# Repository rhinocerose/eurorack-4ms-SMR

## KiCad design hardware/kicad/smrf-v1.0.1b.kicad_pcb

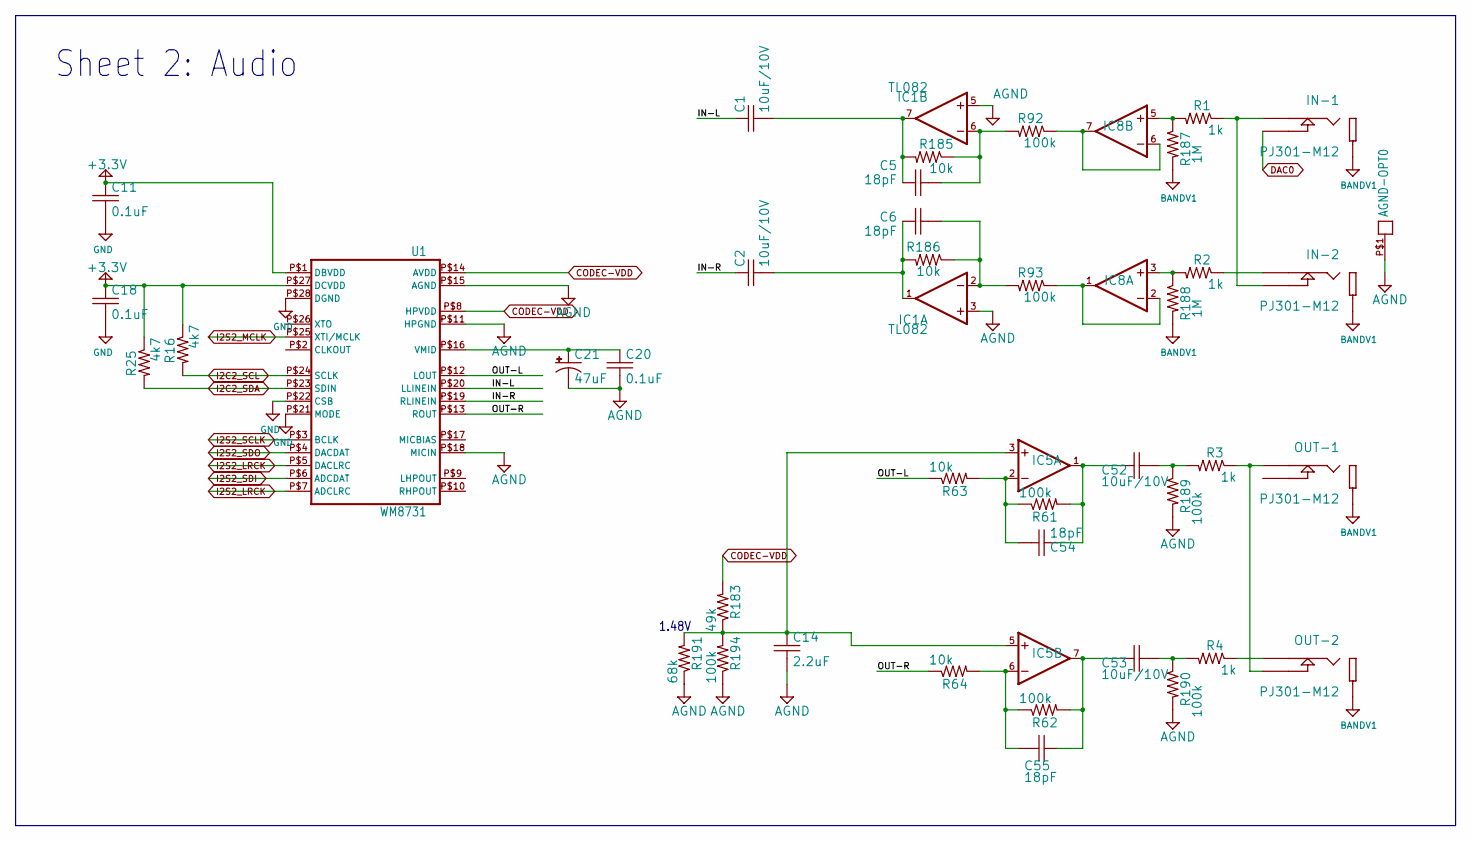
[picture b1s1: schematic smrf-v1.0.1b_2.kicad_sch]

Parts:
AGND-OPT0: PAD-06
C1, C2, C52, C53: 10uF/10V; C0603
C5, C6, C54, C55: 18pF; C0603
C11, C18, C20: 0.1uF; C0603
C14: 2.2uF; C0603
C21: 47uF; C-POL-5
IC1, IC5, IC8: TL082; TSSOP8
IN-1, IN-2: PJ301-M12; PJ301M-12-FIX
OUT-1, OUT-2: PJ301-M12; PJ301M-12-FIX
R1, R2, R3, R4: 1k; R0603
R16, R25: 4k7; R0603
R61, R62, R92, R93, R189, R190, R194: 100k; R0603
R63, R64, R185, R186: 10k; R0603
R183: 49k; R0603
R187, R188: 1M; R0603
R191: 68k; R0603
U1: WM8731; 28-SSOP

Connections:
+3.3V: C11.1, C18.1, R16.1, R25.1, U1.P$1 (DBVDD), U1.P$27 (DCVDD); also elsewhere on the board
AGND: AGND-OPT0.P$1, C14.2, C20.2, C21.-, IC1.3 (+IN), IC1.5 (+IN), R189.2, R190.2, R191.1, R194.1, U1.P$11 (HPGND), U1.P$15 (AGND), U1.P$18 (MICIN); also elsewhere on the board
CODEC-VDD: R183.2, U1.P$8 (HPVDD), U1.P$14 (AVDD); also elsewhere on the board
DAC0: IN-1.3 (TIP-SW); also elsewhere on the board
GND: C11.2, C18.2, IN-1.2 (SLEEVE), IN-2.2 (SLEEVE), OUT-1.2 (SLEEVE), OUT-2.2 (SLEEVE), R187.2, R188.2, U1.P$21 (MODE), U1.P$22 (CSB), U1.P$28 (DGND); also elsewhere on the board
I2C2_SCL: R16.2, U1.P$24 (SCLK); also elsewhere on the board
I2C2_SDA: R25.2, U1.P$23 (SDIN); also elsewhere on the board
I2S2_LRCK: U1.P$5 (DACLRC), U1.P$7 (ADCLRC); also elsewhere on the board
I2S2_MCLK: U1.P$25 (XTI/MCLK); also elsewhere on the board
I2S2_SCLK: U1.P$3 (BCLK); also elsewhere on the board
I2S2_SDI: U1.P$6 (ADCDAT); also elsewhere on the board
I2S2_SDO: U1.P$4 (DACDAT); also elsewhere on the board
IN-L: C1.1, U1.P$20 (LLINEIN)
IN-R: C2.1, U1.P$19 (RLINEIN)
unnamed: OUT-2.1 (TIP), R4.1
unnamed: OUT-1.1 (TIP), OUT-2.3 (TIP-SW), R3.1
unnamed: IN-2.1 (TIP), R2.1
unnamed: C6.2, IC1.2 (-IN), R93.2, R186.1
unnamed: C20.1, C21.+, U1.P$16 (VMID)
unnamed: C54.2, IC5.2 (-IN), R61.1, R63.2
unnamed: C5.2, IC1.6 (-IN), R92.2, R185.1
unnamed: IN-1.1 (TIP), IN-2.3 (TIP-SW), R1.1
unnamed: C1.2, C5.1, IC1.7 (OUT), R185.2
unnamed: C2.2, C6.1, IC1.1 (OUT), R186.2
unnamed: C52.1, C54.1, IC5.1 (OUT), R61.2
unnamed: C55.2, IC5.6 (-IN), R62.1, R64.2
unnamed: C53.1, C55.1, IC5.7 (OUT), R62.2
unnamed: IC8.5 (+IN), R1.2, R187.1
unnamed: IC8.3 (+IN), R2.2, R188.1
unnamed: IC8.6 (-IN), IC8.7 (OUT), R92.1
unnamed: IC8.1 (OUT), IC8.2 (-IN), R93.1
unnamed: C52.2, R3.2, R189.1
unnamed: C53.2, R4.2, R190.1
OUT-L: R63.1, U1.P$12 (LOUT)
OUT-R: R64.1, U1.P$13 (ROUT)
VOUTOFFSET: C14.1, IC5.3 (+IN), IC5.5 (+IN), R183.1, R191.2, R194.2

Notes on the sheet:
Sheet 2: Audio
1.48V

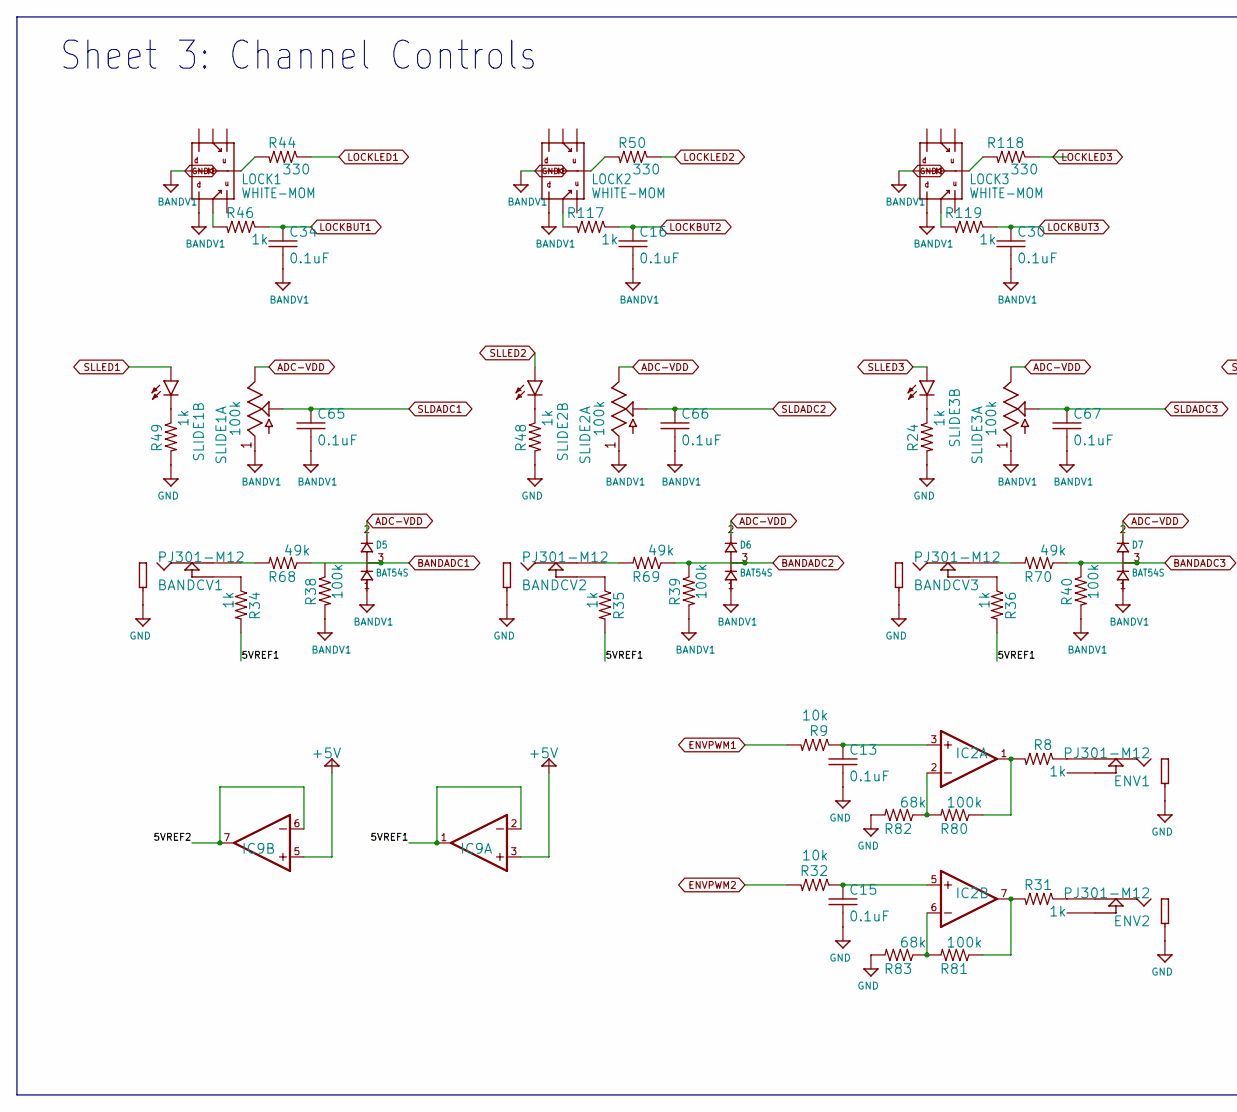
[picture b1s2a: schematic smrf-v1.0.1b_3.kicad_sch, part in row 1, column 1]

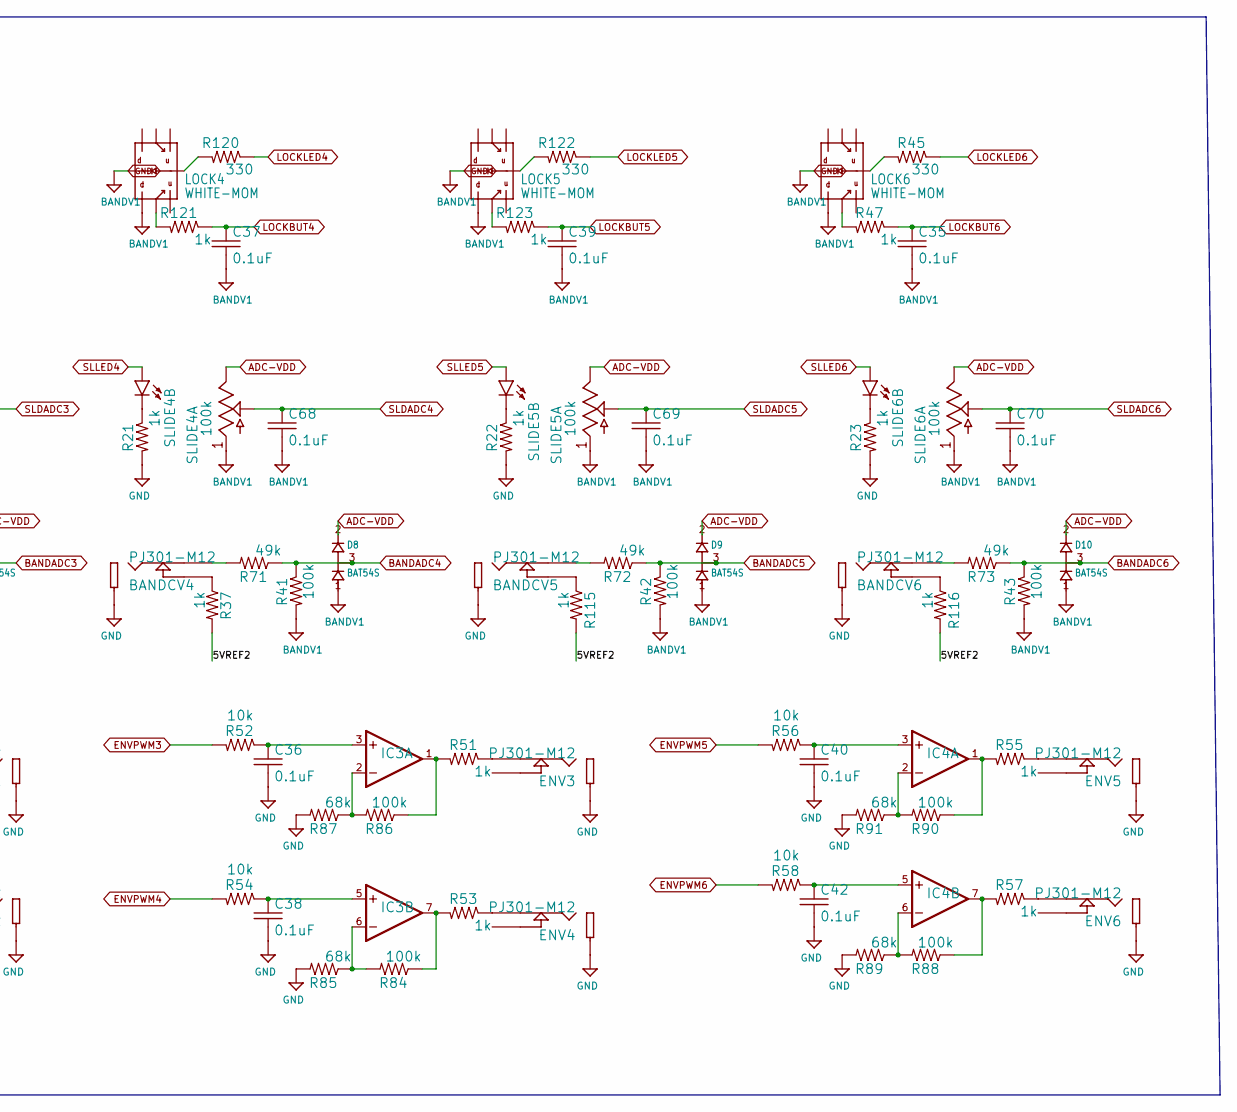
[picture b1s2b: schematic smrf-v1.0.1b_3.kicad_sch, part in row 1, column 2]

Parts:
BANDCV1, BANDCV2, BANDCV3, BANDCV4, BANDCV5, BANDCV6: PJ301-M12; PJ301M-12-FIX
C13, C15, C16, C30, C34, C35, C36, C37, C38, C39, C40, C42, C65, C66, C67, C68, C69, C70: 0.1uF; C0603
D5, D6, D7, D8, D9, D10: BAT54S; SOT23
ENV1, ENV2, ENV3, ENV4, ENV5, ENV6: PJ301-M12; PJ301M-12-FIX
IC2, IC3, IC4, IC9: TL082; TSSOP8
LOCK1, LOCK2, LOCK3, LOCK4, LOCK5, LOCK6: WHITE-MOM; BUTTON-LED-PB61303
R8, R21, R22, R23, R24, R31, R34, R35, R36, R37, R46, R47, R48, R49, R51, R53, R55, R57, R115, R116, R117, R119, R121, R123: 1k; R0603
R9, R32, R52, R54, R56, R58: 10k; R0603
R38, R39, R40, R41, R42, R43, R80, R81, R84, R86, R88, R90: 100k; R0603
R44, R45, R50, R118, R120, R122: 330; R0603
R68, R69, R70, R71, R72, R73: 49k; R0603
R82, R83, R85, R87, R89, R91: 68k; R0603
SLIDE1, SLIDE2, SLIDE3, SLIDE4, SLIDE5, SLIDE6: 100k; POT-SLIDER-ALPHA-RA2045F-20

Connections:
5VREF1: IC9.1 (OUT), IC9.2 (-IN), R34.2, R35.2, R36.2
5VREF2: IC9.6 (-IN), IC9.7 (OUT), R37.2, R115.2, R116.2
+5V: IC9.3 (+IN), IC9.5 (+IN); also elsewhere on the board
ADC-VDD: D5.2 (CATHODE), D6.2 (CATHODE), D7.2 (CATHODE), D8.2 (CATHODE), D9.2 (CATHODE), D10.2 (CATHODE), SLIDE1.P$3 (3), SLIDE2.P$3 (3), SLIDE3.P$3 (3), SLIDE4.P$3 (3), SLIDE5.P$3 (3), SLIDE6.P$3 (3); also elsewhere on the board
BANDADC1: D5.3 (COMMON), R38.1, R68.1; also elsewhere on the board
BANDADC2: D6.3 (COMMON), R39.1, R69.1; also elsewhere on the board
BANDADC3: D7.3 (COMMON), R40.1, R70.1; also elsewhere on the board
BANDADC4: D8.3 (COMMON), R41.1, R71.1; also elsewhere on the board
BANDADC5: D9.3 (COMMON), R42.1, R72.1; also elsewhere on the board
BANDADC6: D10.3 (COMMON), R43.1, R73.1; also elsewhere on the board
ENVPWM1: R9.2; also elsewhere on the board
ENVPWM2: R32.2; also elsewhere on the board
ENVPWM3: R52.2; also elsewhere on the board
ENVPWM4: R54.2; also elsewhere on the board
ENVPWM5: R56.2; also elsewhere on the board
ENVPWM6: R58.2; also elsewhere on the board
GND: BANDCV1.2 (SLEEVE), BANDCV2.2 (SLEEVE), BANDCV3.2 (SLEEVE), BANDCV4.2 (SLEEVE), BANDCV5.2 (SLEEVE), BANDCV6.2 (SLEEVE), C13.2, C15.2, C16.2, C30.2, C34.2, C35.2, C36.2, C37.2, C38.2, C39.2, C40.2, C42.2, C65.2, C66.2, C67.2, C68.2, C69.2, C70.2, D5.1 (ANODE), D6.1 (ANODE), D7.1 (ANODE), D8.1 (ANODE), D9.1 (ANODE), D10.1 (ANODE), ENV1.2 (SLEEVE), ENV2.2 (SLEEVE), ENV3.2 (SLEEVE), ENV4.2 (SLEEVE), ENV5.2 (SLEEVE), ENV6.2 (SLEEVE), LOCK1.P$6, LOCK1.P$8, LOCK2.P$6, LOCK2.P$8, LOCK3.P$6, LOCK3.P$8, LOCK4.P$6, LOCK4.P$8, LOCK5.P$6, LOCK5.P$8, LOCK6.P$6, LOCK6.P$8, R21.2, R22.2, R23.2, R24.2, R38.2, R39.2, R40.2, R41.2, R42.2, R43.2, R48.2, R49.2, R82.2, R83.2, R85.2, R87.2, R89.2, R91.2, SLIDE1.P$1 (1), SLIDE2.P$1 (1), SLIDE3.P$1 (1), SLIDE4.P$1 (1), SLIDE5.P$1 (1), SLIDE6.P$1 (1); also elsewhere on the board
LOCKBUT1: C34.1, R46.1; also elsewhere on the board
LOCKBUT2: C16.1, R117.1; also elsewhere on the board
LOCKBUT3: C30.1, R119.1; also elsewhere on the board
LOCKBUT4: C37.1, R121.1; also elsewhere on the board
LOCKBUT5: C39.1, R123.1; also elsewhere on the board
LOCKBUT6: C35.1, R47.1; also elsewhere on the board
LOCKLED1: R44.1; also elsewhere on the board
LOCKLED2: R50.1; also elsewhere on the board
LOCKLED3: R118.1; also elsewhere on the board
LOCKLED4: R120.1; also elsewhere on the board
LOCKLED5: R122.1; also elsewhere on the board
LOCKLED6: R45.1; also elsewhere on the board
unnamed: ENV1.1 (TIP), R8.1
unnamed: BANDCV1.3 (TIP-SW), R34.1
unnamed: BANDCV2.3 (TIP-SW), R35.1
unnamed: BANDCV3.3 (TIP-SW), R36.1
unnamed: BANDCV4.3 (TIP-SW), R37.1
unnamed: BANDCV5.3 (TIP-SW), R115.1
unnamed: BANDCV6.3 (TIP-SW), R116.1
unnamed: R21.1, SLIDE4.P$LEDC (C)
unnamed: R22.1, SLIDE5.P$LEDC (C)
unnamed: LOCK2.P$7, R50.2
unnamed: LOCK2.P$5, R117.2
unnamed: C13.1, IC2.3 (+IN), R9.1
unnamed: R23.1, SLIDE6.P$LEDC (C)
unnamed: BANDCV1.1 (TIP), R68.2
unnamed: LOCK1.P$7, R44.2
unnamed: BANDCV2.1 (TIP), R69.2
unnamed: LOCK6.P$7, R45.2
unnamed: R24.1, SLIDE3.P$LEDC (C)
unnamed: BANDCV3.1 (TIP), R70.2
unnamed: LOCK1.P$5, R46.2
unnamed: R48.1, SLIDE2.P$LEDC (C)
unnamed: BANDCV4.1 (TIP), R71.2
unnamed: LOCK6.P$5, R47.2
unnamed: R49.1, SLIDE1.P$LEDC (C)
unnamed: BANDCV5.1 (TIP), R72.2
unnamed: BANDCV6.1 (TIP), R73.2
unnamed: IC2.1 (OUT), R8.2, R80.1
unnamed: ENV2.1 (TIP), R31.1
unnamed: C15.1, IC2.5 (+IN), R32.1
unnamed: IC2.7 (OUT), R31.2, R81.1
unnamed: ENV3.1 (TIP), R51.1
unnamed: C36.1, IC3.3 (+IN), R52.1
unnamed: IC3.1 (OUT), R51.2, R86.1
unnamed: ENV4.1 (TIP), R53.1
unnamed: C38.1, IC3.5 (+IN), R54.1
unnamed: IC3.7 (OUT), R53.2, R84.1
unnamed: ENV5.1 (TIP), R55.1
unnamed: C40.1, IC4.3 (+IN), R56.1
unnamed: IC4.1 (OUT), R55.2, R90.1
unnamed: ENV6.1 (TIP), R57.1
unnamed: C42.1, IC4.5 (+IN), R58.1
unnamed: IC4.7 (OUT), R57.2, R88.1
unnamed: IC4.2 (-IN), R90.2, R91.1
unnamed: IC3.6 (-IN), R84.2, R85.1
unnamed: IC3.2 (-IN), R86.2, R87.1
unnamed: IC4.6 (-IN), R88.2, R89.1
unnamed: IC2.6 (-IN), R81.2, R83.1
unnamed: IC2.2 (-IN), R80.2, R82.1
unnamed: LOCK3.P$7, R118.2
unnamed: LOCK3.P$5, R119.2
unnamed: LOCK4.P$7, R120.2
unnamed: LOCK4.P$5, R121.2
unnamed: LOCK5.P$7, R122.2
unnamed: LOCK5.P$5, R123.2
SLDADC1: C65.1, SLIDE1.P$2 (2); also elsewhere on the board
SLDADC2: C66.1, SLIDE2.P$2 (2); also elsewhere on the board
SLDADC3: C67.1, SLIDE3.P$2 (2); also elsewhere on the board
SLDADC4: C68.1, SLIDE4.P$2 (2); also elsewhere on the board
SLDADC5: C69.1, SLIDE5.P$2 (2); also elsewhere on the board
SLDADC6: C70.1, SLIDE6.P$2 (2); also elsewhere on the board
SLLED1: SLIDE1.P$LEDA (A); also elsewhere on the board
SLLED2: SLIDE2.P$LEDA (A); also elsewhere on the board
SLLED3: SLIDE3.P$LEDA (A); also elsewhere on the board
SLLED4: SLIDE4.P$LEDA (A); also elsewhere on the board
SLLED5: SLIDE5.P$LEDA (A); also elsewhere on the board
SLLED6: SLIDE6.P$LEDA (A); also elsewhere on the board

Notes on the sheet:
Sheet 3: Channel Controls

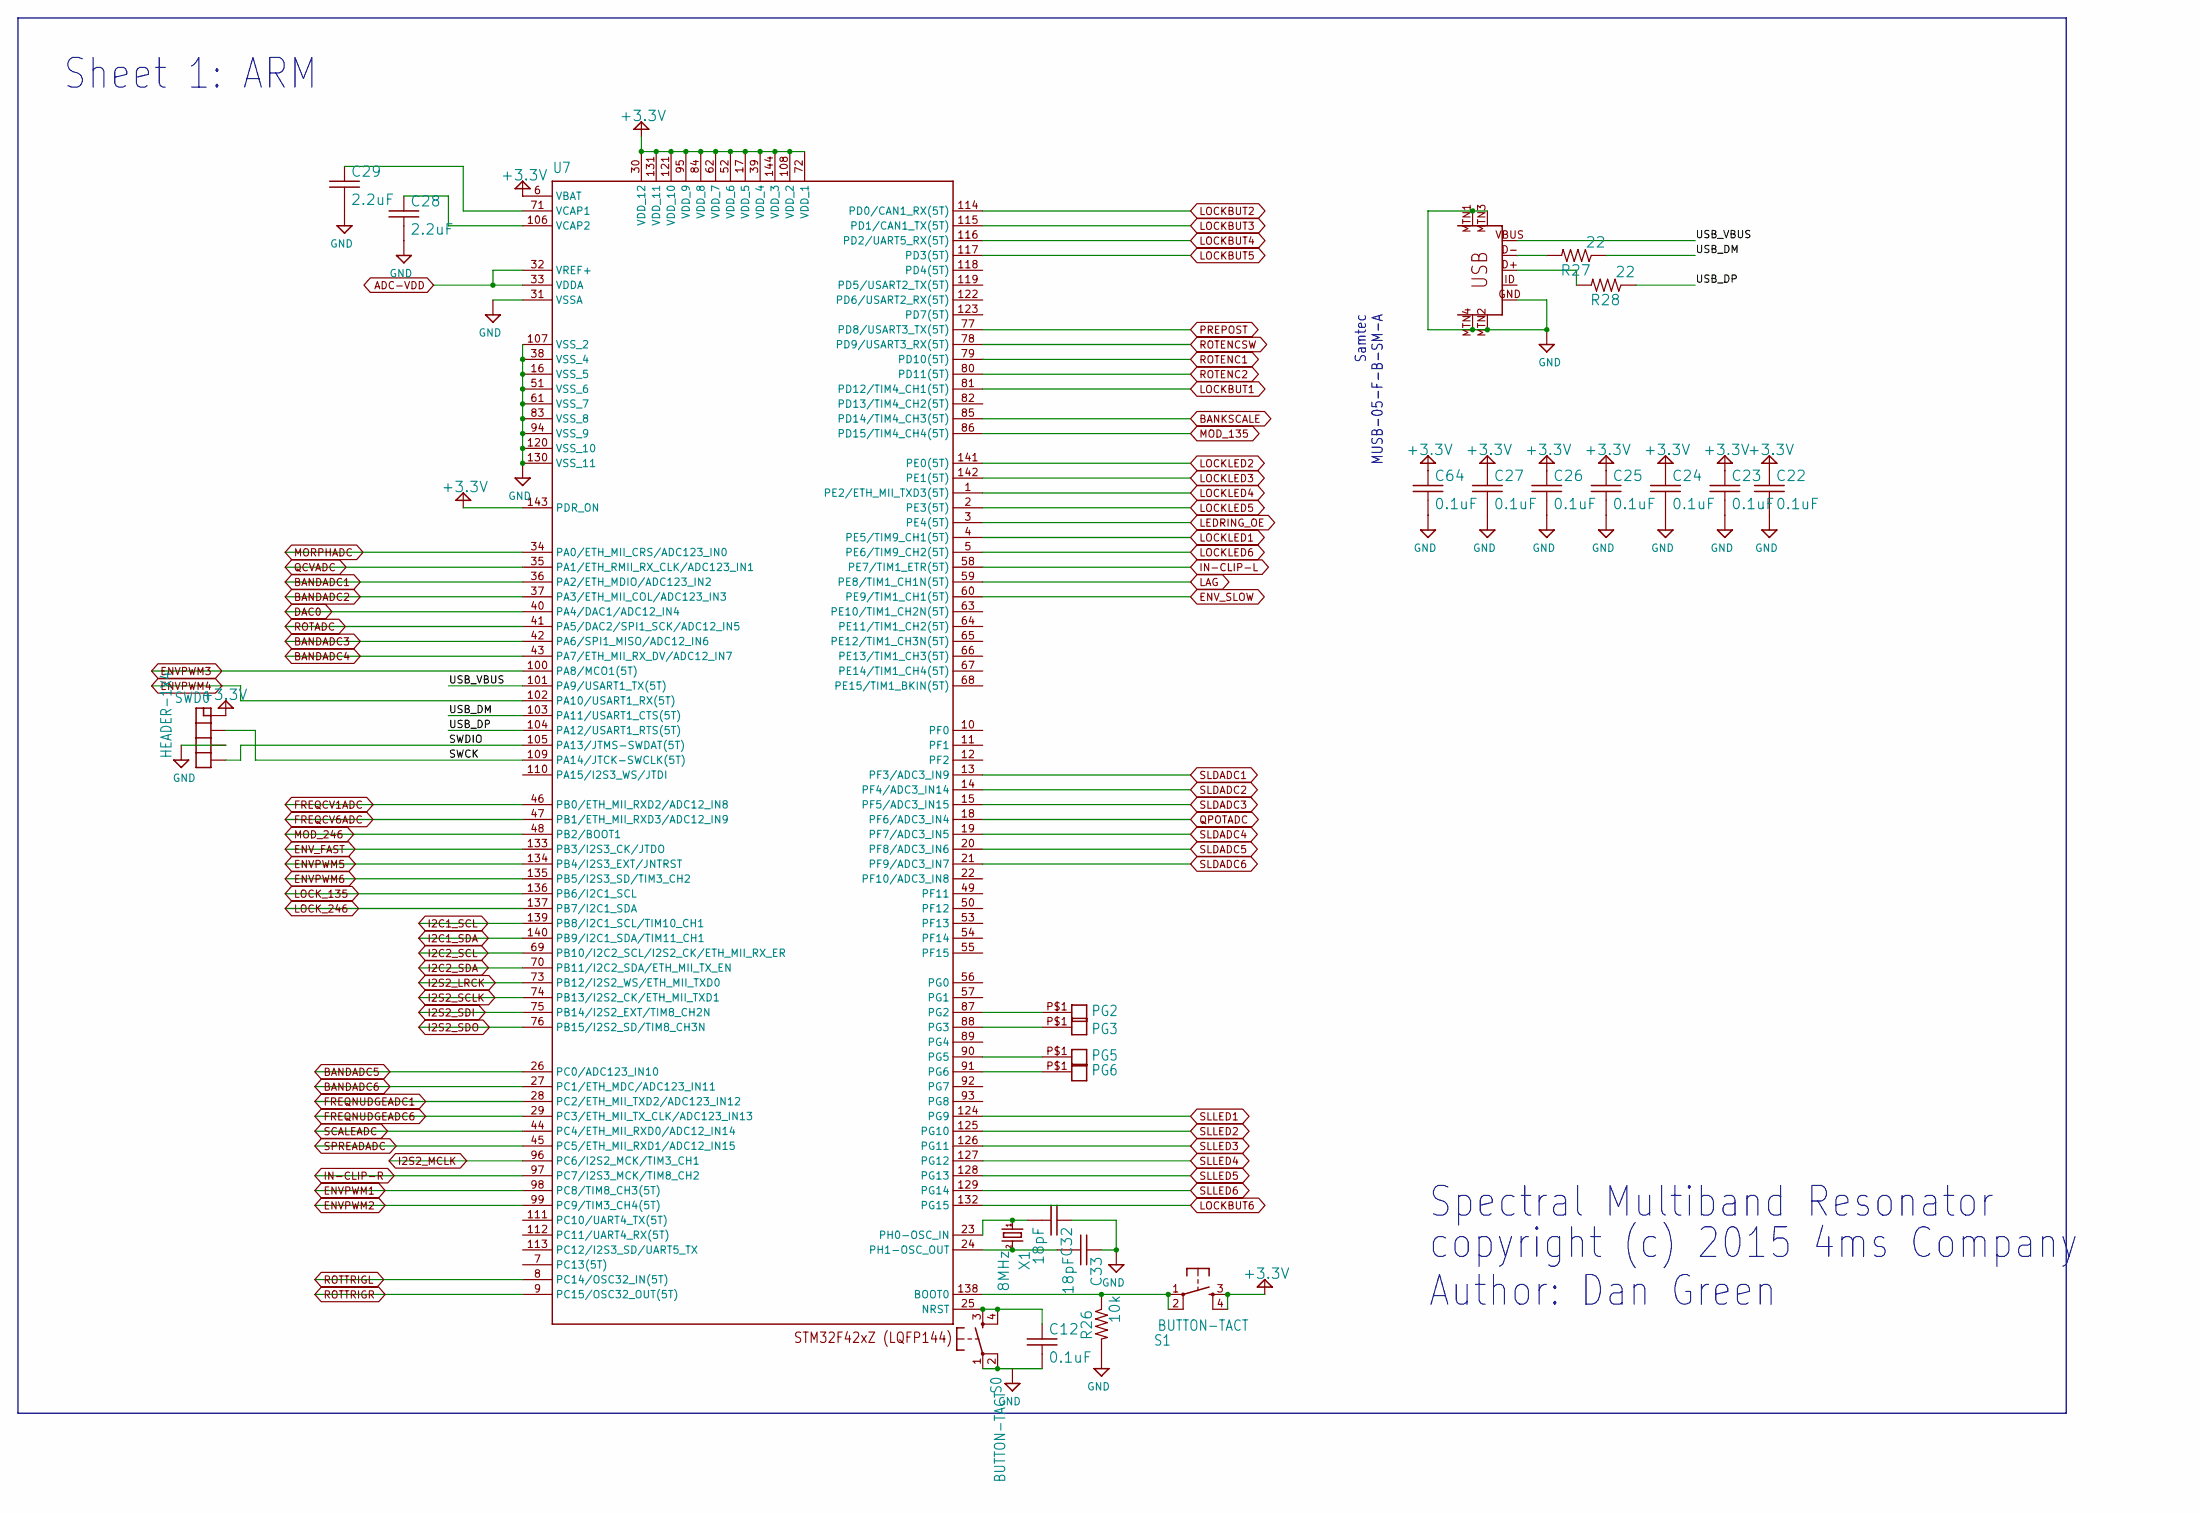
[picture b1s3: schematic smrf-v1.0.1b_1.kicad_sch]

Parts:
C12, C22, C23, C24, C25, C26, C27, C64: 0.1uF; C0603
C28, C29: 2.2uF; C0603
C32, C33: 18pF; C0603
PG2, PG3, PG5, PG6: PAD-06
R26: 10k; R0603
R27, R28: 22; R0603
S0, S1: BUTTON-TACT; BUTTON-TACT-SKQG
SWD0: HEADER-1X4; HEADER-1X4-TH
U7: STM32F427ZG; LQFP144
U$1: USB-MINIB-5PIN; USB-MINIB
X1: 8MHz; HC-49_US

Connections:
+3.3V: C22.1, C23.1, C24.1, C25.1, C26.1, C27.1, C64.1, S1.3, S1.4, SWD0.P$1, U7.6 (VBAT), U7.17 (VDD_5), U7.30 (VDD_12), U7.39 (VDD_4), U7.52 (VDD_6), U7.62 (VDD_7), U7.72 (VDD_1), U7.84 (VDD_8), U7.95 (VDD_9), U7.108 (VDD_2), U7.121 (VDD_10), U7.131 (VDD_11), U7.143 (PDR_ON), U7.144 (VDD_3); also elsewhere on the board
ADC-VDD: U7.32 (VREF+), U7.33 (VDDA); also elsewhere on the board
BANDADC1: U7.36 (PA2/ETH_MDIO/ADC123_IN2); also elsewhere on the board
BANDADC2: U7.37 (PA3/ETH_MII_COL/ADC123_IN3); also elsewhere on the board
BANDADC3: U7.42 (PA6/SPI1_MISO/ADC12_IN6); also elsewhere on the board
BANDADC4: U7.43 (PA7/ETH_MII_RX_DV/ADC12_IN7); also elsewhere on the board
BANDADC5: U7.26 (PC0/ADC123_IN10); also elsewhere on the board
BANDADC6: U7.27 (PC1/ETH_MDC/ADC123_IN11); also elsewhere on the board
BANKSCALE: U7.85 (PD14/TIM4_CH3(5T)); also elsewhere on the board
DAC0: U7.40 (PA4/DAC1/ADC12_IN4); also elsewhere on the board
ENVPWM1: U7.98 (PC8/TIM8_CH3(5T)); also elsewhere on the board
ENVPWM2: U7.99 (PC9/TIM3_CH4(5T)); also elsewhere on the board
ENVPWM3: U7.100 (PA8/MCO1(5T)); also elsewhere on the board
ENVPWM4: U7.102 (PA10/USART1_RX(5T)); also elsewhere on the board
ENVPWM5: U7.134 (PB4/I2S3_EXT/JNTRST); also elsewhere on the board
ENVPWM6: U7.135 (PB5/I2S3_SD/TIM3_CH2); also elsewhere on the board
ENV_FAST: U7.133 (PB3/I2S3_CK/JTDO); also elsewhere on the board
ENV_SLOW: U7.60 (PE9/TIM1_CH1(5T)); also elsewhere on the board
FREQCV1ADC: U7.46 (PB0/ETH_MII_RXD2/ADC12_IN8); also elsewhere on the board
FREQCV6ADC: U7.47 (PB1/ETH_MII_RXD3/ADC12_IN9); also elsewhere on the board
FREQNUDGEADC1: U7.28 (PC2/ETH_MII_TXD2/ADC123_IN12); also elsewhere on the board
FREQNUDGEADC6: U7.29 (PC3/ETH_MII_TX_CLK/ADC123_IN13); also elsewhere on the board
GND: C12.2, C22.2, C23.2, C24.2, C25.2, C26.2, C27.2, C28.2, C29.2, C32.1, C33.1, C64.2, R26.2, S0.1, S0.2, SWD0.P$3, U7.16 (VSS_5), U7.31 (VSSA), U7.38 (VSS_4), U7.51 (VSS_6), U7.61 (VSS_7), U7.83 (VSS_8), U7.94 (VSS_9), U7.107 (VSS_2), U7.120 (VSS_10), U7.130 (VSS_11), U$1.GND, U$1.MTN1 (MTN2), U$1.MTN2 (MTN3), U$1.MTN3 (MTN1), U$1.MTN4; also elsewhere on the board
I2C1_SCL: U7.139 (PB8/I2C1_SCL/TIM10_CH1); also elsewhere on the board
I2C1_SDA: U7.140 (PB9/I2C1_SDA/TIM11_CH1); also elsewhere on the board
I2C2_SCL: U7.69 (PB10/I2C2_SCL/I2S2_CK/ETH_MII_RX_ER); also elsewhere on the board
I2C2_SDA: U7.70 (PB11/I2C2_SDA/ETH_MII_TX_EN); also elsewhere on the board
I2S2_LRCK: U7.73 (PB12/I2S2_WS/ETH_MII_TXD0); also elsewhere on the board
I2S2_MCLK: U7.96 (PC6/I2S2_MCK/TIM3_CH1); also elsewhere on the board
I2S2_SCLK: U7.74 (PB13/I2S2_CK/ETH_MII_TXD1); also elsewhere on the board
I2S2_SDI: U7.75 (PB14/I2S2_EXT/TIM8_CH2N); also elsewhere on the board
I2S2_SDO: U7.76 (PB15/I2S2_SD/TIM8_CH3N); also elsewhere on the board
IN-CLIP-L: U7.58 (PE7/TIM1_ETR(5T)); also elsewhere on the board
IN-CLIP-R: U7.97 (PC7/I2S3_MCK/TIM8_CH2); also elsewhere on the board
LAG: U7.59 (PE8/TIM1_CH1N(5T)); also elsewhere on the board
LEDRING_OE: U7.3 (PE4(5T)); also elsewhere on the board
LOCKBUT1: U7.81 (PD12/TIM4_CH1(5T)); also elsewhere on the board
LOCKBUT2: U7.114 (PD0/CAN1_RX(5T)); also elsewhere on the board
LOCKBUT3: U7.115 (PD1/CAN1_TX(5T)); also elsewhere on the board
LOCKBUT4: U7.116 (PD2/UART5_RX(5T)); also elsewhere on the board
LOCKBUT5: U7.117 (PD3(5T)); also elsewhere on the board
LOCKBUT6: U7.132 (PG15); also elsewhere on the board
LOCKLED1: U7.4 (PE5/TIM9_CH1(5T)); also elsewhere on the board
LOCKLED2: U7.141 (PE0(5T)); also elsewhere on the board
LOCKLED3: U7.142 (PE1(5T)); also elsewhere on the board
LOCKLED4: U7.1 (PE2/ETH_MII_TXD3(5T)); also elsewhere on the board
LOCKLED5: U7.2 (PE3(5T)); also elsewhere on the board
LOCKLED6: U7.5 (PE6/TIM9_CH2(5T)); also elsewhere on the board
LOCK_135: U7.136 (PB6/I2C1_SCL); also elsewhere on the board
LOCK_246: U7.137 (PB7/I2C1_SDA); also elsewhere on the board
MOD_135: U7.86 (PD15/TIM4_CH4(5T)); also elsewhere on the board
MOD_246: U7.48 (PB2/BOOT1); also elsewhere on the board
MORPHADC: U7.34 (PA0/ETH_MII_CRS/ADC123_IN0); also elsewhere on the board
unnamed: R27.2, U$1.D-
unnamed: R28.2, U$1.D+
unnamed: C32.2, U7.23 (PH0-OSC_IN), X1.1
unnamed: C28.1, U7.106 (VCAP2)
unnamed: C29.1, U7.71 (VCAP1)
unnamed: R26.1, S1.1, S1.2, U7.138 (BOOT0)
unnamed: C33.2, U7.24 (PH1-OSC_OUT), X1.2
unnamed: PG2.P$1, U7.87 (PG2)
unnamed: PG3.P$1, U7.88 (PG3)
unnamed: PG6.P$1, U7.91 (PG6)
unnamed: PG5.P$1, U7.90 (PG5)
NRST: C12.1, S0.3, S0.4, U7.25 (NRST)
PREPOST: U7.77 (PD8/USART3_TX(5T)); also elsewhere on the board
QCVADC: U7.35 (PA1/ETH_RMII_RX_CLK/ADC123_IN1); also elsewhere on the board
QPOTADC: U7.18 (PF6/ADC3_IN4); also elsewhere on the board
ROTADC: U7.41 (PA5/DAC2/SPI1_SCK/ADC12_IN5); also elsewhere on the board
ROTENC1: U7.79 (PD10(5T)); also elsewhere on the board
ROTENC2: U7.80 (PD11(5T)); also elsewhere on the board
ROTENCSW: U7.78 (PD9/USART3_RX(5T)); also elsewhere on the board
ROTTRIGL: U7.8 (PC14/OSC32_IN(5T)); also elsewhere on the board
ROTTRIGR: U7.9 (PC15/OSC32_OUT(5T)); also elsewhere on the board
SCALEADC: U7.44 (PC4/ETH_MII_RXD0/ADC12_IN14); also elsewhere on the board
SLDADC1: U7.13 (PF3/ADC3_IN9); also elsewhere on the board
SLDADC2: U7.14 (PF4/ADC3_IN14); also elsewhere on the board
SLDADC3: U7.15 (PF5/ADC3_IN15); also elsewhere on the board
SLDADC4: U7.19 (PF7/ADC3_IN5); also elsewhere on the board
SLDADC5: U7.20 (PF8/ADC3_IN6); also elsewhere on the board
SLDADC6: U7.21 (PF9/ADC3_IN7); also elsewhere on the board
SLLED1: U7.124 (PG9); also elsewhere on the board
SLLED2: U7.125 (PG10); also elsewhere on the board
SLLED3: U7.126 (PG11); also elsewhere on the board
SLLED4: U7.127 (PG12); also elsewhere on the board
SLLED5: U7.128 (PG13); also elsewhere on the board
SLLED6: U7.129 (PG14); also elsewhere on the board
SPREADADC: U7.45 (PC5/ETH_MII_RXD1/ADC12_IN15); also elsewhere on the board
SWCK: SWD0.P$2, U7.109 (PA14/JTCK-SWCLK(5T))
SWDIO: SWD0.P$4, U7.105 (PA13/JTMS-SWDAT(5T))
USB_DM: R27.1, U7.103 (PA11/USART1_CTS(5T))
USB_DP: R28.1, U7.104 (PA12/USART1_RTS(5T))
USB_VBUS: U7.101 (PA9/USART1_TX(5T)), U$1.VBUS

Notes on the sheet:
Sheet 1: ARM
Samtec MUSB-05-F-B-SM-A
Spectral Multiband Resonator
copyright (c) 2015 4ms Company Author: Dan Green
